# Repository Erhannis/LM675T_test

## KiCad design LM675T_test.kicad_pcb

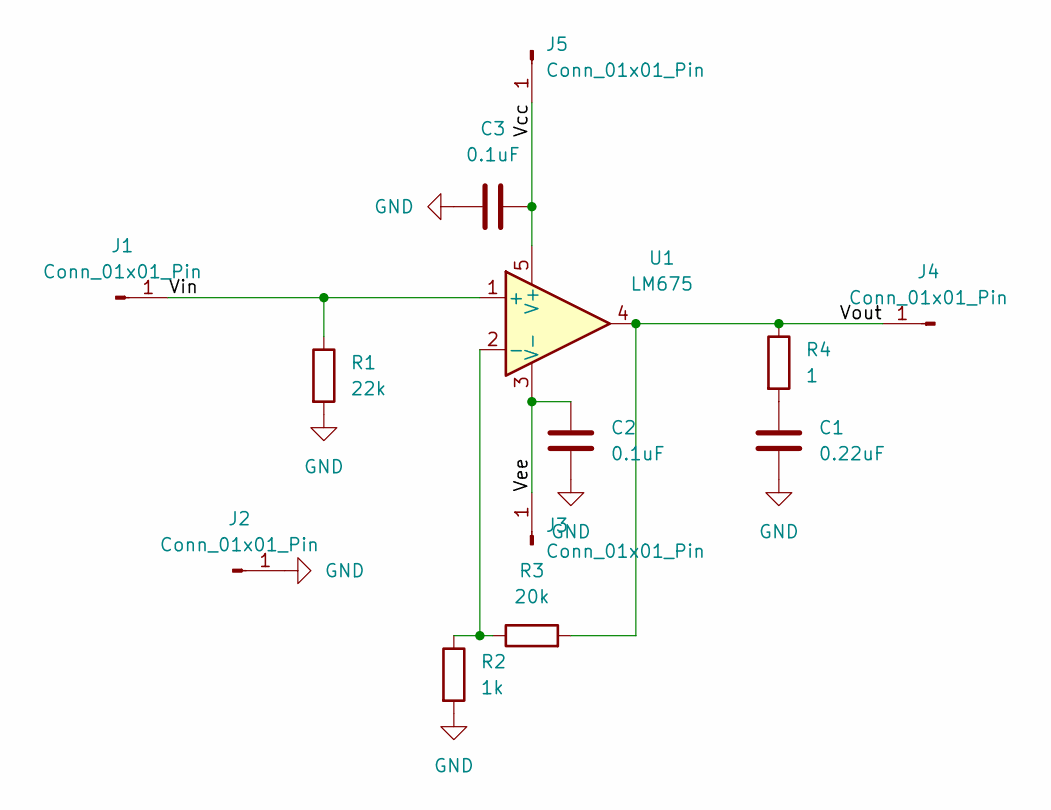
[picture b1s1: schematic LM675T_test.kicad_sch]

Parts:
C1: 0.22uF; C_0805_2012Metric; LCSC C5378
C2, C3: 0.1uF; C_0805_2012Metric; LCSC C49678
J1, J2, J3, J4, J5: Conn_01x01_Pin; PinHeader_1x01_P2.54mm_Vertical
R1: 22k; R_0805_2012Metric; LCSC C17560
R2: 1k; R_0805_2012Metric; LCSC C17513
R3: 20k; R_0805_2012Metric; LCSC C4328
R4: 1; R_0805_2012Metric; LCSC C25271
U1: LM675; TO-220-5_P3.4x3.8mm_StaggerOdd_Lead7.13mm_TabDown

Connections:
/Vcc: C3.1, J5.1, U1.5 (V+)
/Vee: C2.1, J3.1, U1.3 (V-)
/Vin: J1.1, R1.1, U1.1 (+)
/Vout: J4.1, R3.2, R4.1, U1.4
GND: C1.2, C2.2, C3.2, J2.1, R1.2, R2.2
unnamed: C1.1, R4.2
unnamed: R2.1, R3.1, U1.2 (-)

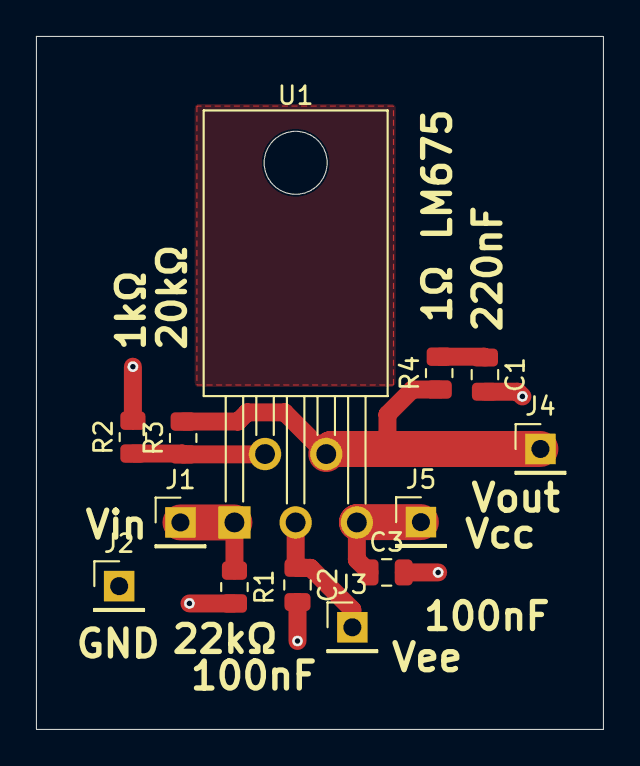
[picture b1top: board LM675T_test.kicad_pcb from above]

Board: 2 copper layers, 31.5 x 38.5 mm, 13 parts (0 on the bottom side), 7 nets.

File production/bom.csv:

Designator,Footprint,Quantity,Value,LCSC Part #
C1,0805,1,0.22uF,
"C2, C3",0805,2,0.1uF,
"J1, J2, J3, J4, J5",PinHeader_1x01_P2.54mm_Vertical,5,Conn_01x01_Pin,
R1,0805,1,22k,
R2,0805,1,1k,
R3,0805,1,20k,
R4,0805,1,1,
U1,TO-220-5_P3.4x3.8mm_StaggerOdd_Lead7.13mm_TabDown,1,LM675,

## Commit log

2025-05-11 Committing an unfinished test board for the LM675T reference schematic
2025-05-14 Finished board layout
2025-05-16 Resized board. Also wrote a script to convert drill files into svgs for lasering.
2025-05-16 Tweaks. Sending to JLCPCB as a last ditch test.
